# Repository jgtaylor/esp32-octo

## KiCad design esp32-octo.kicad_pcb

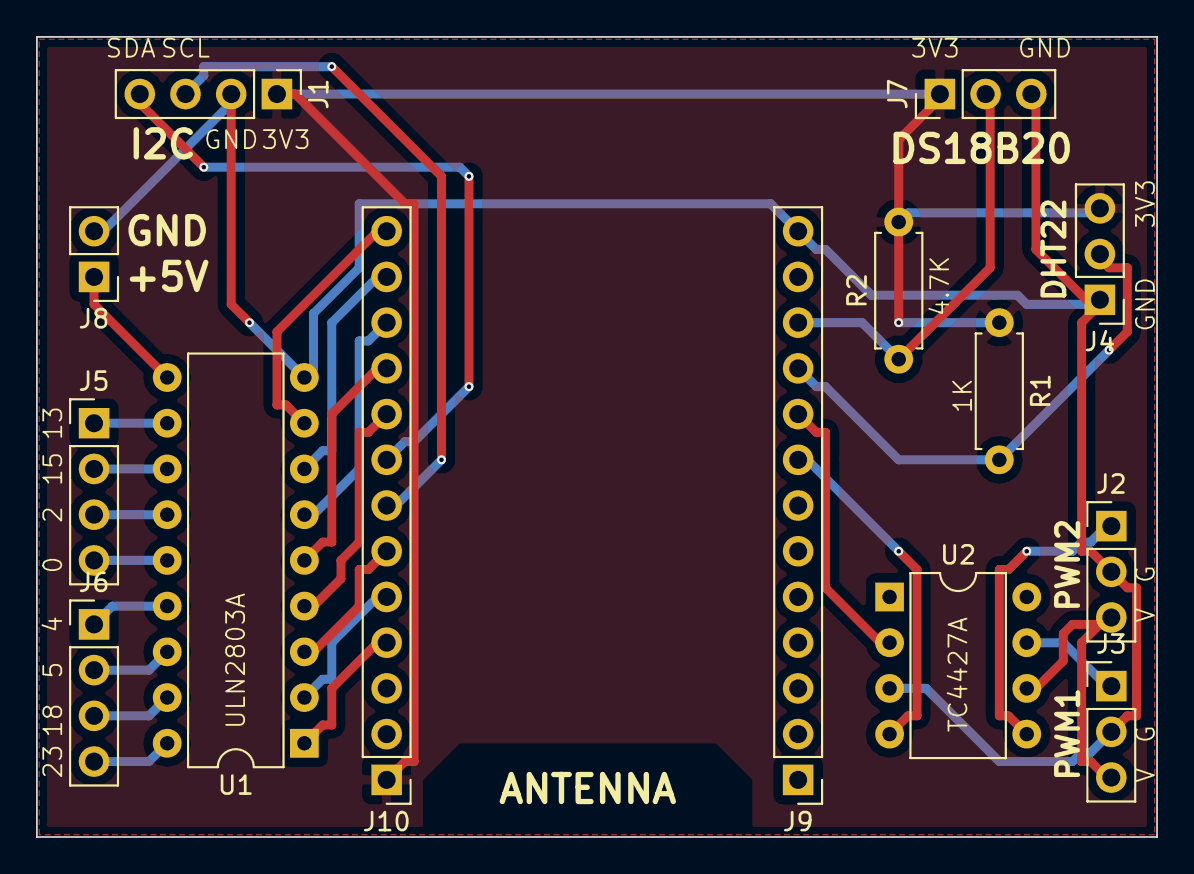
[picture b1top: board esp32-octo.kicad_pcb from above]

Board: 2 copper layers, 62.2 x 44.5 mm, 14 parts (0 on the bottom side), 28 nets.

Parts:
J1: I2C; Pin_Header_Straight_1x04_Pitch2.54mm
J2: PWM2; Pin_Header_Straight_1x03_Pitch2.54mm
J3: PWM1; Pin_Header_Straight_1x03_Pitch2.54mm
J4: DHT22; Pin_Header_Straight_1x03_Pitch2.54mm
J5: P5-8; Pin_Header_Straight_1x04_Pitch2.54mm
J6: P1-4; Pin_Header_Straight_1x04_Pitch2.54mm
J7: DS18B20; Pin_Header_Straight_1x03_Pitch2.54mm
J8: +5V; Pin_Header_Straight_1x02_Pitch2.54mm
J9, J10: CONN_01X13; Pin_Header_Straight_1x13_Pitch2.54mm
R1: 1k; R_Axial_DIN0207_L6.3mm_D2.5mm_P7.62mm_Horizontal
R2: 4.7k; R_Axial_DIN0207_L6.3mm_D2.5mm_P7.62mm_Horizontal
U1: ULN2803A; DIP-18_W7.62mm
U2: TC4427AEOA; DIP-8_W7.62mm

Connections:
+3V3: J1.1, J4.3, J7.1, J10.1, R1.1, R2.2
+5V: J8.1, U1.10
D0: J10.10, U1.5
D2: J10.11, U1.6
D4: J10.9, U1.4
D5: J10.6, U1.3
D13: J10.13, U1.8
D14: J7.2, J9.11, R2.1
D15: J10.12, U1.7
D16: J1.4, J10.8
D17: J1.3, J10.7
D18: J10.5, U1.2
D23: J10.4, U1.1
D25: J9.8, U2.4
D26: J9.9, U2.2
D27: J4.2, J9.10, R1.2
GND: J1.2, J2.2, J3.2, J4.1, J7.3, J8.2, J9.13, U1.9, U2.3
unnamed: J2.1, U2.5
unnamed: J3.1, U2.7
unnamed: J5.1, U1.11
unnamed: J5.2, U1.12
unnamed: J5.3, U1.13
unnamed: J5.4, U1.14
unnamed: J6.1, U1.15
unnamed: J6.2, U1.16
unnamed: J6.3, U1.17
unnamed: J6.4, U1.18
VDD: J2.3, J3.3, U2.6

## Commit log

2018-03-14 initial checkin
2018-03-14 initial
